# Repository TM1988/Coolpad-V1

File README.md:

# Coolpad-V1    

Coolpad-V1 is a macropad for [Blueprint](https://blueprint.hackclub.com) by [Hack Club](https://hackclub.com)! 

It has a clean 6-key (2x3) layout powered by Seeed Studio XIAO-RP2040 with CircuitPython firmware. It includes a rotary encoder and 0.91" OLED display in a minimalist white box-like case.

This is my first hardware based project so I was kind of clueless half of the time but Shoutout to Hack Club Slack for all the help!

## Features
- 6 Keys in 2x3 matrix layout
- 2 Part Case + OLED Cover
- Clean white design
- 0.91" 128x64 OLED Screen
- EC11 Rotary Encoder
- Powered by Seeed XIAO-RP2040 Microcontroller
- 60° Angle
- Custom Firmware & App (WIP)

## Challenges
I had no idea how to use KiCad or Fusion 360 so I had to learn both of them. I also had a lot of trouble with fitting the parts to my case and I had to start over twice!

## CAD
### How it Works
Designed in [Fusion360](https://www.autodesk.com/products/fusion-360/overview) around an ecport of my KiCad PCB. Case is supposed to be held together with 4 M3x16mm screws and the OLED cover will be glued on? (Might change once I get the parts)

### Parts
- **Bottom case**: Houses PCB & Components
- **Top case**: Switch & Encoder cutouts, Bars to hold the OLED module
- **OLED cover**: Holds the OLED in place and hides OLED PCB

## PCB and Schematic
Designed in [KiCad](https://www.kicad.org/) with 2x3 key matrix.
### Pcb:

### Schematic:

### Files
[PCB Design Files](https://github.com/TM1988/Coolpad-V1/tree/main/PCB)

## Firmware
- [x] Basic Firmware (CircuitPython)
- [ ] Basic App (Web/Local) for Macros, Layers, Graphics
- [ ] Automatic Standby Timer
- [ ] Active App Detection for Macros
- [ ] OLED Graphics + Macros Mode
- [ ] More once I think of new things

CircuitPython base running on XIAO-RP2040. I have planned a web/local (haven't decided which) app will handle macro switching, layer control, and app detection, graphics, etc.

[Firmware Files](https://github.com/TM1988/Coolpad-V1/tree/main/Firmware)

## BOM
- 1x - 0.91" OLED Display (I2C: SDA-SCL-VCC-GND)
- 1x - EC11 Rotary Encoder
- 6x - Blank DSA Keycaps
- 6x - Cherry MX Switches
- 1x - Seeed Studio XIAO-RP2040
- 4x - M3x16mm Screws
- 1x - 3D Printed Case (Top + Bottom + OLED Cover)

## More Links

[3D Models](https://github.com/TM1988/Coolpad-V1/tree/main/Assets/3D%20Models) | [Rendered Images](https://github.com/TM1988/Coolpad-V1/tree/main/Assets/Render%20Images)

Most 3D Models of the components can be found [here](https://grabcad.com) (I think)

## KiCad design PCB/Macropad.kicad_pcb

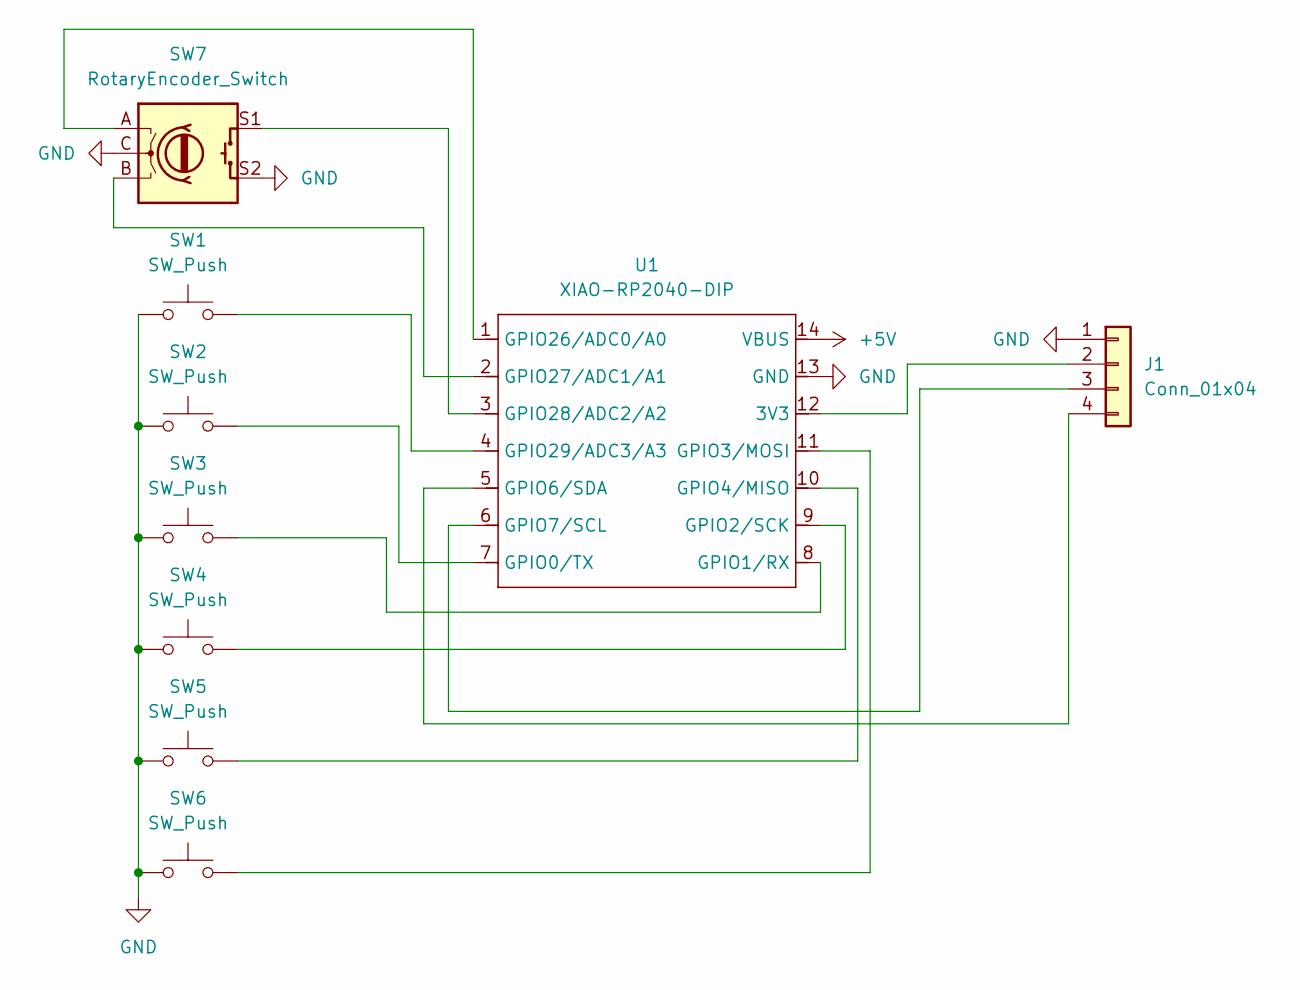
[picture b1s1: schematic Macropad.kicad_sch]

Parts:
J1: Conn_01x04; SSD1306-0.91-OLED-4pin-128x32
SW1, SW2, SW3, SW4, SW5, SW6: SW_Push; SW_Cherry_MX_1.00u_PCB
SW7: RotaryEncoder_Switch; RotaryEncoder_Alps_EC11E-Switch_Vertical_H20mm
U1: XIAO-RP2040-DIP

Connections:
+5V: U1.14 (VBUS)
GND: J1.1, SW1.1, SW2.1, SW3.1, SW4.1, SW5.1, SW6.1, SW7.C, SW7.S2, U1.13 (GND)
unnamed: J1.2, U1.12 (3V3)
unnamed: J1.3, U1.6 (GPIO7/SCL)
unnamed: J1.4, U1.5 (GPIO6/SDA)
unnamed: SW2.2, U1.7 (GPIO0/TX)
unnamed: SW3.2, U1.8 (GPIO1/RX)
unnamed: SW4.2, U1.9 (GPIO2/SCK)
unnamed: SW6.2, U1.11 (GPIO3/MOSI)
unnamed: SW5.2, U1.10 (GPIO4/MISO)
unnamed: SW7.A, U1.1 (GPIO26/ADC0/A0)
unnamed: SW7.B, U1.2 (GPIO27/ADC1/A1)
unnamed: SW7.S1, U1.3 (GPIO28/ADC2/A2)
unnamed: SW1.2, U1.4 (GPIO29/ADC3/A3)

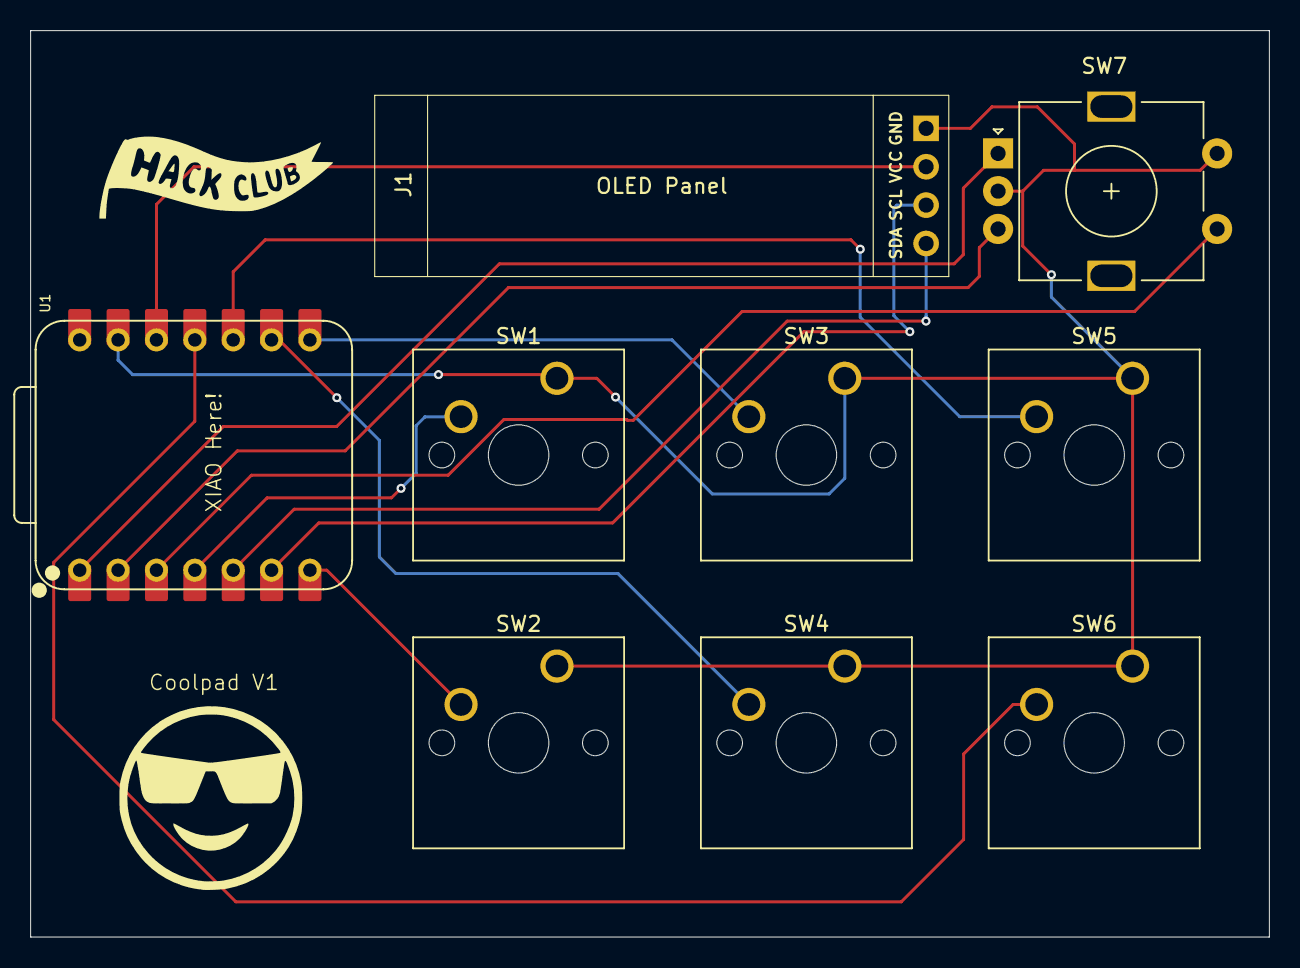
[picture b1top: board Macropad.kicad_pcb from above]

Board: 2 copper layers, 82.0 x 60.0 mm, 9 parts (0 on the bottom side), 13 nets.

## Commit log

2025-12-30 Fix formatting in project title in README
2025-12-30 Initial Commit of Files
2025-12-30 Add fully assembled 3d model
2025-12-31 Update README.md and small structure changes
2025-12-31 Fixed a few things in the README
2026-01-04 New 3D Models
2026-01-04 Cleaned up pcb traces + optimized 3D Models for strength
